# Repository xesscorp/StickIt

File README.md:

StickIt! Board and Modules
=================================================================

The StickIt! main motherboard and attached modules are used with the XuLA & XuLA2 FPGA boards to provide additional functions. 
The documentation, FPGA projects, firmware, schematic and PCB files are included in the subdirectories.

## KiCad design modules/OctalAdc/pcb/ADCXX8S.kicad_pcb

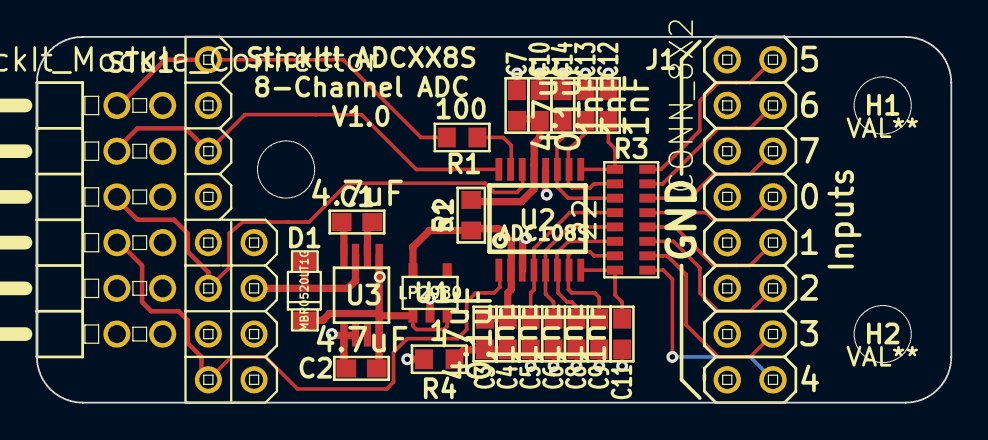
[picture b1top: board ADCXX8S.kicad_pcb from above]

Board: 2 copper layers, 50.8 x 20.3 mm, 26 parts (0 on the bottom side), 29 nets.

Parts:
C1, C2, C3, C7: 4.7uF; rcl-C0603
C4, C10: 0.1uF; rcl-C0603
C5, C6, C8, C9, C11, C12, C13, C14: 1nF; rcl-C0603
D1: MBR0520LT1G; SOD-123
H1, H2: VAL**; HOLE
J1: CONN_8X2; pinhead-2X08
R1: 100; rcl-R0603
R2: 51; rcl-R0603
R3: 22; xess-742C163
R4: 1; rcl-R0603
STK1: StickIt_Module_Connector; xess-STICKIT-HEADER1
U1: LP2980; SOT23-5
U2: ADC108S; TSSOP16
U3: LM2660; SSOP8

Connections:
/AVDD: C3.1, C4.1, R2.2, U1.5, U2.2
/DIN: STK1.BIO3, STK1.CIO3, U2.14
/DOUT: R1.2, STK1.BIO1, STK1.CIO8
/DVDD: C7.1, C10.1, R2.1, U2.13
/GND: C2.2, C5.2, C6.2, C7.2, C8.2, C9.2, C10.2, C11.2, C12.2, C13.2, C14.2, J1.1, J1.3, J1.5, J1.7, J1.9, J1.11, J1.13, J1.15, R4.2, STK1.AGND, STK1.BGND, STK1.CGND, U1.2, U2.3, U2.12, U3.5, U3.6
/IN0: J1.8, R3.13
/IN1: J1.10, R3.12
/IN2: J1.12, R3.11
/IN3: J1.14, R3.10
/IN4: J1.16, R3.9
/IN5: J1.2, R3.16
/IN6: J1.4, R3.15
/IN7: J1.6, R3.14
/SCLK: STK1.BIO2, STK1.CIO6, U2.16
/VCC: D1.1, STK1.+3V3, STK1.APWR, STK1.BPWR, U3.3
/~CS: STK1.BIO4, STK1.CIO1, U2.1
unnamed: C1.1, U3.2
unnamed: C1.2, U3.4
unnamed: C2.1, D1.2, U1.1, U1.3, U3.1, U3.8
unnamed: C3.2, C4.2, R4.1
unnamed: C5.1, R3.4, U2.4
unnamed: C6.1, R3.5, U2.5
unnamed: C8.1, R3.6, U2.6
unnamed: C9.1, R3.7, U2.7
unnamed: C11.1, R3.8, U2.8
unnamed: C12.1, R3.1, U2.9
unnamed: C13.1, R3.2, U2.10
unnamed: C14.1, R3.3, U2.11
unnamed: R1.1, U2.15

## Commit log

2012-01-18 Initial checkin.
2012-01-18 Added README file for StickIt! projects.
2012-01-19 Needed this file for the project.
2012-01-19 Needed for project.
2012-01-19 Fixed display of h, n and u.
2012-01-19 Changed location of some needed files to local directory.
2012-01-19 Removed some unneeded pin assignments.
2012-01-19 Recompiled to reflect previous source changes.
2012-01-19 Added to local directory.
2012-01-19 Added local versions of common.vhd and leddigits.vhd.
2012-01-19 Recompiled to reflect previous changes.
2012-01-19 Deleted unnecessary testbench files.
2012-01-19 Removed testbench files from project.
2012-01-20 Updated UCF files.
2012-01-21 Changed signal names to make ButtonScanner easier to understand.
2012-01-21 Recompiled to reflect source changes.
2012-01-22 Made LedDigits.vhd easier to read and understand and recompiled it.
2012-02-04 Added Inkscape file of button scanning circuit.
2012-02-04 Added PS/2 interface module.
2012-02-04 - Removed "All rights reserved" from copyright statement of StickIt! manuals. - Reduced image resolution to reduce manual sizes.
2012-02-10 Added StickIt! VGA module.
2012-02-10 Replaced PNG photo with JPEG.
2012-05-19 Added module for displaying 32-bit hex number.
2012-09-22 Switched from POD to markdown for README file.
2012-09-22 Removing POD version of README.
2012-09-22 Renamed README so it will be recognized as a markdown file.
2012-09-22 README edit.
2012-09-22 Added README for test/demo FPGA design of StickIt! Button module.
2012-09-22 Changed ISE project file name.
2012-09-22 Added README for test/demo FPGA design of StickIt! LED Digits module.
2012-09-22 Changed Wing connector name.
2012-09-22 Renamed some directories.
2012-09-22 Renamed ISE project file.
2012-09-22 Added README file and changed ISE project file name.
2012-09-22 Corrected references from button scanner to LED digits.
2012-09-22 Renamed FPGA test example directory.
2012-09-22 Added README and renamed some files.
2012-09-22 Changes to README files.
2012-09-23 Updated project to use most-current SDRAM controller module.
2012-09-23 Modifications to manual for StickIt! V2.0 board.
2012-09-23 StickIt! board V2.0
2012-09-23 Updated to reflect StickIt! board V2.0.
2012-09-24 V2.0 with rounded corners.
2012-09-24 V2.0 manual.
2012-09-29 Moved SMT components to top edge.
2012-10-19 StickIt! Buttons 2.0 PCB
2012-10-19 StickIt! LED Digits 2.0 PCB
2012-10-19 StickIt! PS/2 2.0 PCB
2012-11-12 Updated VGA and StickIt headers with the changes from xess.lbr.
2012-12-07 Changed manufacturer for the 2x6 Pmod socket on the StickIt! main board.
2012-12-11 Changed manufacturer & part number for the Pmod socket.
2012-12-11 Centered schematic within page frame.
2012-12-11 Revised manual for changes in StickIt! 3.0 board.
2013-02-02 Added StickIt! module PCB template.
2013-10-03 Added design files for StickIt! DIP Switch module.
2013-10-03 Updated template for StickIt! module with wiring and traces between the PMOD and WING headers.
2013-10-03 Changed extension on README file so it would display properly on Github.
2013-10-15 Added StickIt! Audio I/O module files.
2013-10-15 Added Audio I/O board pin assignments for each StickIt! board WING and PMOD connector.
2013-10-15 Added Audio I/O board README file.
2013-10-17 Updated manual to reflect current V2.0 board.
2013-10-17 Updated manual to reflect V2.0 board.
2013-11-13 Added StickIt! Rotary Encoder module.
2013-11-13 Tweaked StickIt! Audio module schematic.
2013-11-13 Corrected StickIt! Rotary Encoder manual title.
2013-12-01 Added UCF for the rotary encoder example design.
2014-01-06 Added StickIt! MPU-XXXX files.
2014-01-22 Modified FPGA example for the VGA module to use 1024x768 images.
2014-01-22 Fixed VGA design example README.
2014-03-04 Added StickIt!-MPU-9150 module.
2014-03-04 Modified ISE project file to optimize synth for area so this project works with the XuLA2-LX9.
2014-04-10 Converted VGA test to use VHDL library.
2014-04-10 Updated python test program to output some additional diagnostic information.
2014-04-25 Added 8-channel ADC StickIt! board.
2014-04-28 Added alternate settings for sampling just one channel.
2014-05-24 Corrected a spelling error in a comment.
2014-05-24 Added two new example designs for the StickIt! AudioIO board.
2014-05-27 README for audio_hostio application.
2014-05-27 Added README file.
2014-06-23 Changed bitstream generation settings so the bitstream would configure the FPGA correctly.
2014-06-23 Changed pin assignments so rotary encoder could be attached to Wing1 connector.
2014-08-02 Changed 5V regulator to LP2980 in SOT23-5 package.
2014-08-03 Moved part references on silkscreen.
2014-08-22 Updated library name from OctalAdc to ADCXX8S.
2014-09-16 Updated datasampler FPGA project to use VHDL library.
2015-02-06 Change in library file order.
2015-04-24 Corrected horiz and vert sync labels on Wing I/O header.
2015-12-02 Updated project to correct errors induced by changes in online libraries. * Removed references to the 'special' and 'XESS' libraries.
